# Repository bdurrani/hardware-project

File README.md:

## Testing avrdude

```
avrdude -c usbtiny -p atmega328p -C "C:\Program Files (x86)\Arduino\hardware\tools\avr/etc/avrdude.conf"
```

## Set fuses to use external clock with no brownout

```
avrdude -c usbtiny -p atmega328p -C "C:\Program Files (x86)\Arduino\hardware\tools\avr/etc/avrdude.conf" -U lfuse:w:0xff:m -U hfuse:w:0xda:m
```

## Upload using programmer

`Ctrl + Alt + B`

## Power usage

- Blinky sketch with serial write enabled
    - 13.2 mA with LED off
    - 14.00 mA with LED on

## Requirements

- Low power
    - Battery powered using LiPo @ 3.7V

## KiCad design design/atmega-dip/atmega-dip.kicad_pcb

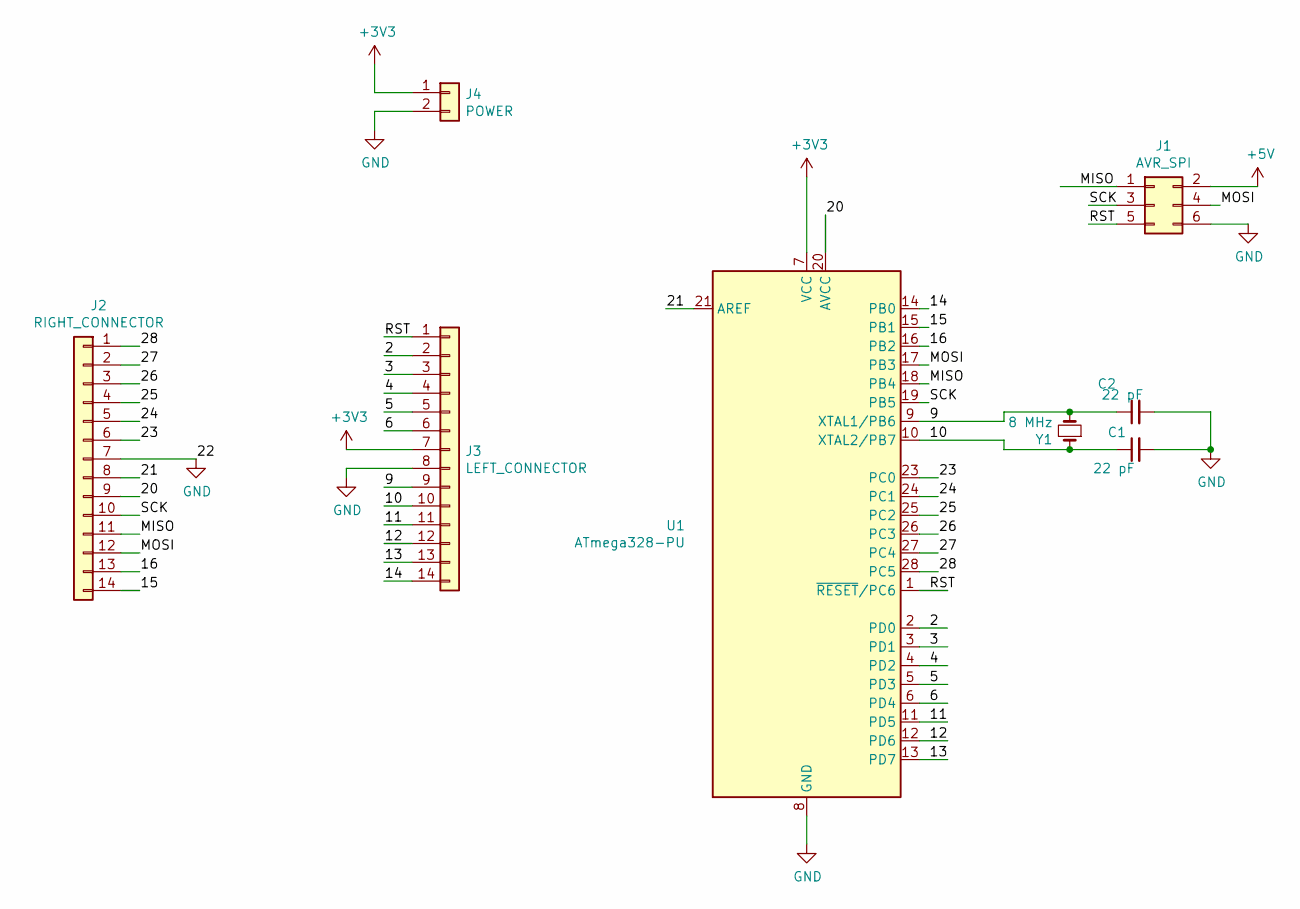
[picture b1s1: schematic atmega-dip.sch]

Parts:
C1, C2: 22 pF; C_Disc_D3.0mm_W2.0mm_P2.50mm
J1: AVR_SPI; IDC-Header_2x03_P2.54mm_Vertical
J2: RIGHT_CONNECTOR; PinHeader_1x14_P2.54mm_Vertical
J3: LEFT_CONNECTOR; PinHeader_1x14_P2.54mm_Vertical
J4: POWER; JST_PH_S2B-PH-K_1x02_P2.00mm_Horizontal
U1: ATmega328-PU; DIP-28_W7.62mm
Y1: 8 MHz; Crystal_HC49-4H_Vertical

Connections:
+3V3: J3.7, J4.1, U1.7 (VCC)
+5V: J1.2
/2: J3.2, U1.2 (PD0)
/3: J3.3, U1.3 (PD1)
/4: J3.4, U1.4 (PD2)
/5: J3.5, U1.5 (PD3)
/6: J3.6, U1.6 (PD4)
/9: C2.1, J3.9, U1.9 (XTAL1/PB6), Y1.2
/10: C1.1, J3.10, U1.10 (XTAL2/PB7), Y1.1
/11: J3.11, U1.11 (PD5)
/12: J3.12, U1.12 (PD6)
/13: J3.13, U1.13 (PD7)
/14: J3.14, U1.14 (PB0)
/15: J2.14, U1.15 (PB1)
/16: J2.13, U1.16 (PB2)
/20: J2.9, U1.20 (AVCC)
/21: J2.8, U1.21 (AREF)
/23: J2.6, U1.23 (PC0)
/24: J2.5, U1.24 (PC1)
/25: J2.4, U1.25 (PC2)
/26: J2.3, U1.26 (PC3)
/27: J2.2, U1.27 (PC4)
/28: J2.1, U1.28 (PC5)
/MISO: J1.1, J2.11, U1.18 (PB4)
/MOSI: J1.4, J2.12, U1.17 (PB3)
/RST: J1.5, J3.1, U1.1 (~RESET~/PC6)
/SCK: J1.3, J2.10, U1.19 (PB5)
GND: C1.2, C2.2, J1.6, J2.7, J3.8, J4.2, U1.8 (GND), U1.22 (GND)

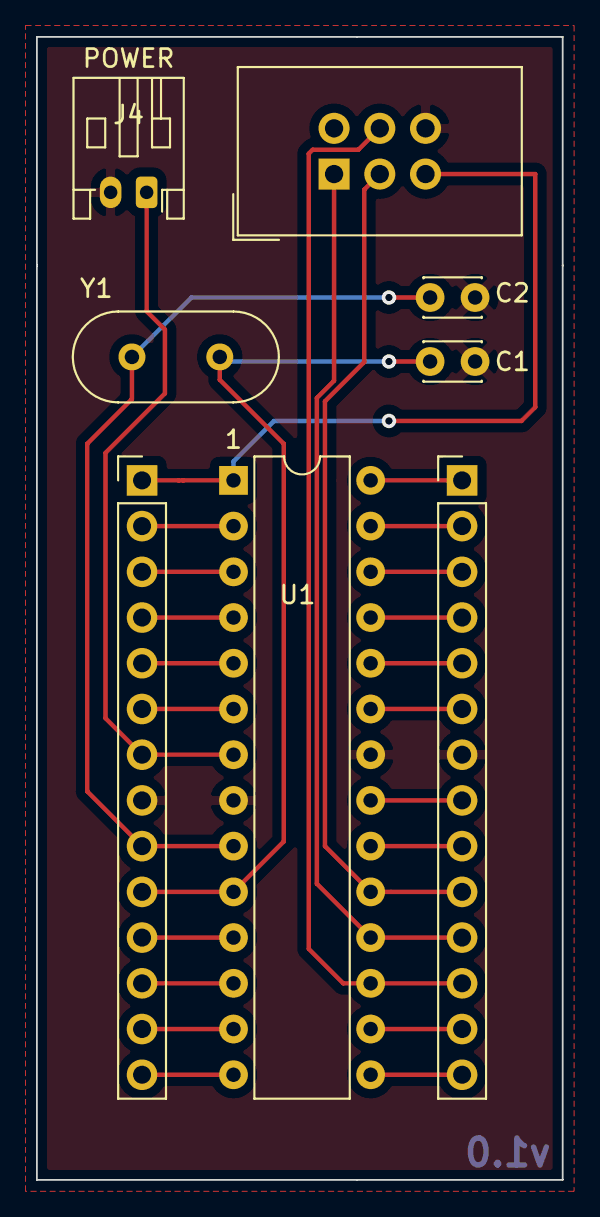
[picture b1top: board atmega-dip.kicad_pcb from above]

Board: 2 copper layers, 29.2 x 63.5 mm, 8 parts (0 on the bottom side), 27 nets.

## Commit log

2019-04-19 documentation
2019-04-19 set up project using arduino plugin for vscode
2019-04-19 add shortcut for uploading via programmer
2019-04-19 write to serial test
2019-04-21 add notes for basic baseline power usage
2019-04-21 ignore ipch folder
2019-04-23 schematic for helper board
2019-04-23 progressing on pcb design
    still need connector for RAW, VCC and GND
2019-04-23 done for the night
2019-04-23 added power connector more pins connected to the header
2019-04-24 connect the rest
2019-04-25 added board edge
2019-04-25 added power net group
2019-04-25 routing is hard
2019-04-26 save work
2019-04-26 got most of the board routed. GND is on layer 2
2019-04-26 everything is wired up. saving before adding a ground plane
2019-04-27 added some text
    still need to verufy breadboard width
2019-04-27 borad is too big. need to shrink it down
2019-04-29 still having routing to do
2019-04-29 some more rerouting
2019-04-29 finish the routing
2019-04-29 add bottom silkscreen
2019-04-30 placed final order
